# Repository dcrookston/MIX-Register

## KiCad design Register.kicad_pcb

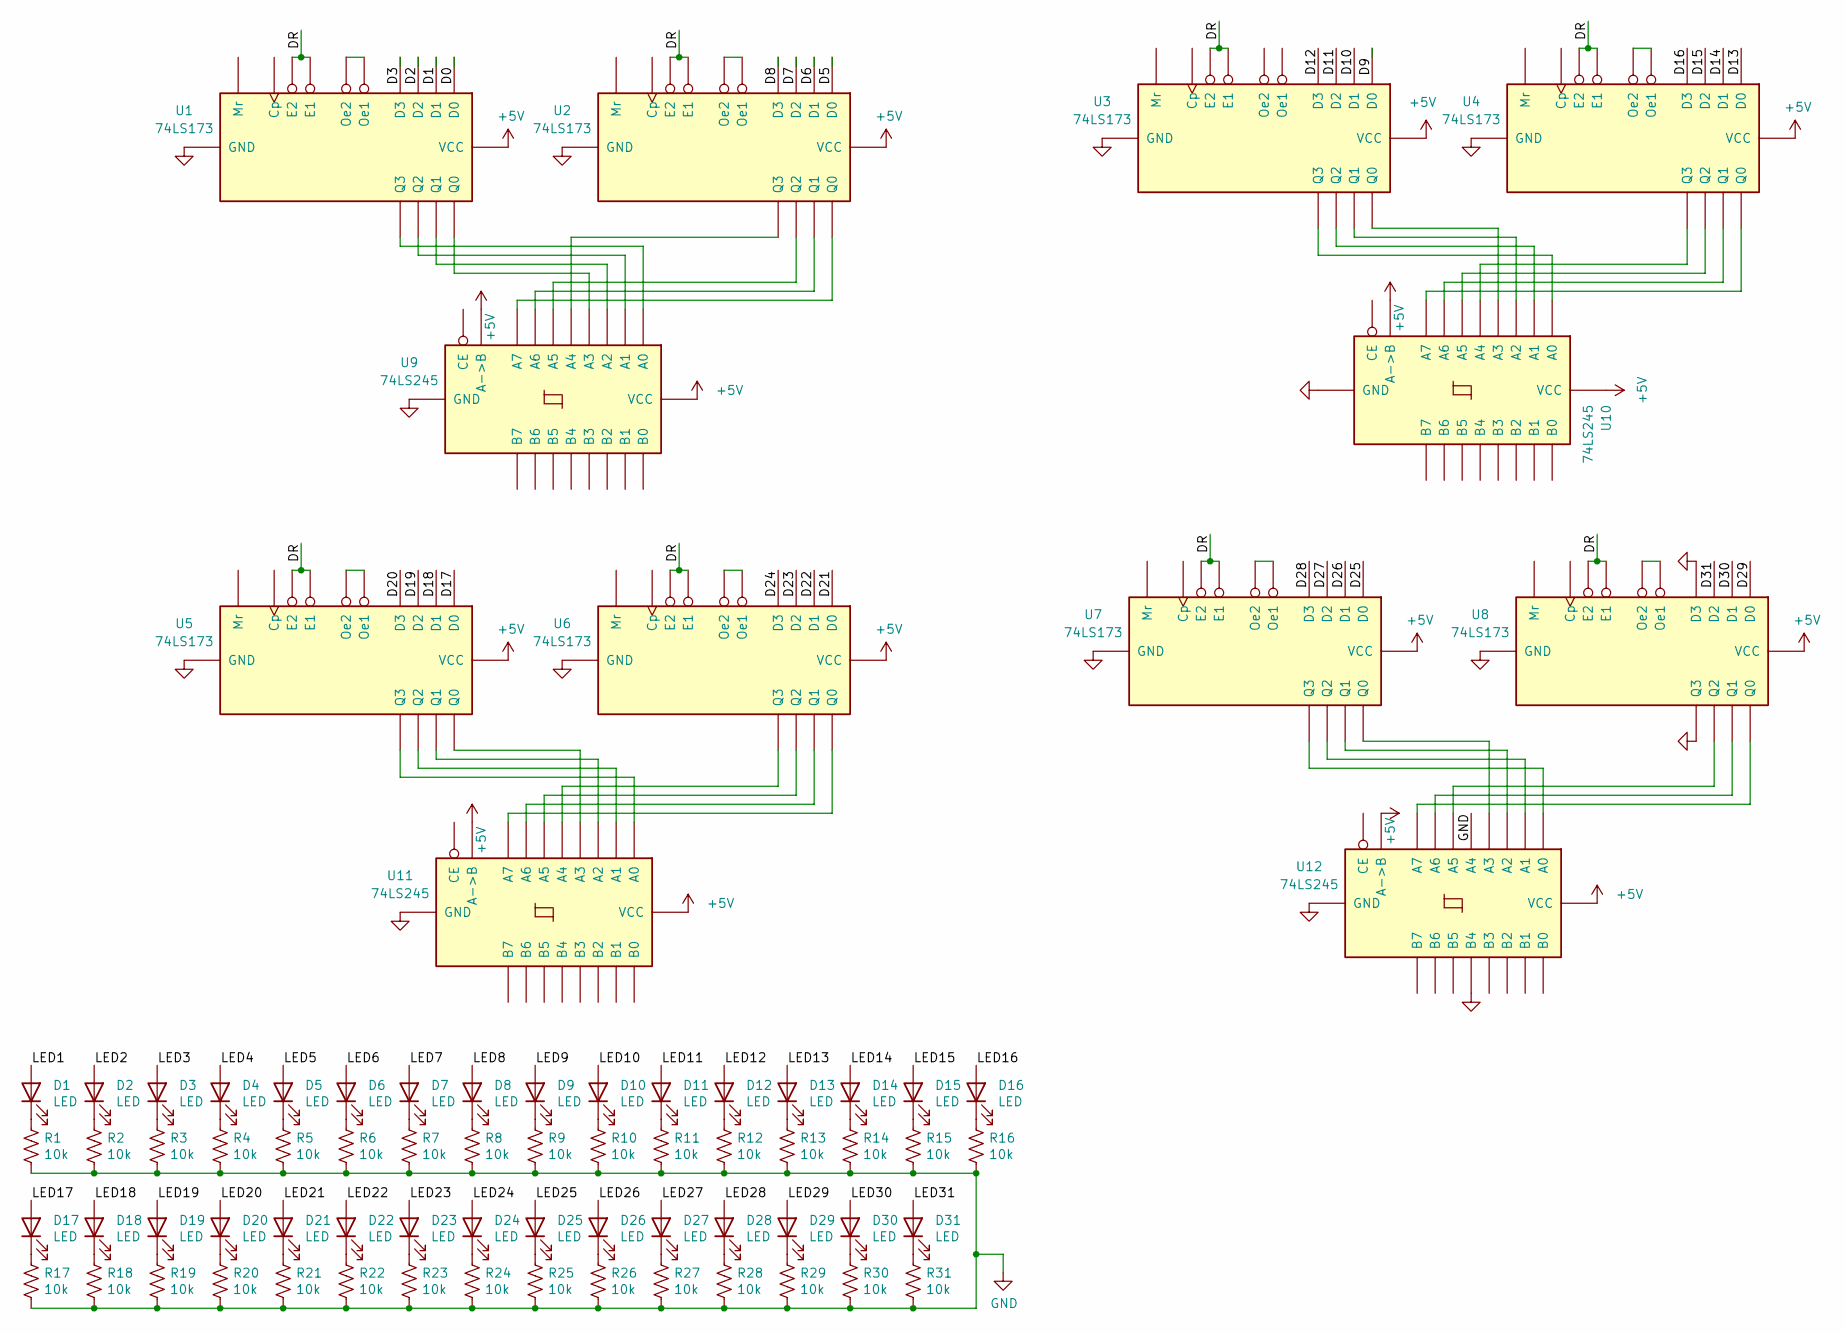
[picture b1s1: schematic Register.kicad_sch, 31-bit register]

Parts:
D1, D2, D3, D4, D5, D6, D7, D8, D9, D10, D11, D12, D13, D14, D15, D16, D17, D18, D19, D20, D21, D22, D23, D24, D25, D26, D27, D28, D29, D30, D31: LED; LED_0402_1005Metric
R1, R2, R3, R4, R5, R6, R7, R8, R9, R10, R11, R12, R13, R14, R15, R16, R17, R18, R19, R20, R21, R22, R23, R24, R25, R26, R27, R28, R29, R30, R31: 10k; R_0402_1005Metric
U1, U2, U3, U4, U5, U6, U7, U8: 74LS173; SOIC-16_3.9x9.9mm_P1.27mm
U9, U10, U11, U12: 74LS245; SOIC-20W_7.5x12.8mm_P1.27mm

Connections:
+5V: U1.16 (VCC), U2.16 (VCC), U3.16 (VCC), U4.16 (VCC), U5.16 (VCC), U6.16 (VCC), U7.16 (VCC), U8.16 (VCC), U9.1 (A->B), U9.20 (VCC), U10.1 (A->B), U10.20 (VCC), U11.1 (A->B), U11.20 (VCC), U12.1 (A->B), U12.20 (VCC)
/D0: U1.14 (D0)
/D1: U1.13 (D1)
/D2: U1.12 (D2)
/D3: U1.11 (D3)
/D5: U2.14 (D0)
/D6: U2.13 (D1)
/D7: U2.12 (D2)
/D8: U2.11 (D3)
/D9: U3.14 (D0)
/D10: U3.13 (D1)
/D11: U3.12 (D2)
/D12: U3.11 (D3)
/D13: U4.14 (D0)
/D14: U4.13 (D1)
/D15: U4.12 (D2)
/D16: U4.11 (D3)
/D17: U5.14 (D0)
/D18: U5.13 (D1)
/D19: U5.12 (D2)
/D20: U5.11 (D3)
/D21: U6.14 (D0)
/D22: U6.13 (D1)
/D23: U6.12 (D2)
/D24: U6.11 (D3)
/D25: U7.14 (D0)
/D26: U7.13 (D1)
/D27: U7.12 (D2)
/D28: U7.11 (D3)
/D29: U8.14 (D0)
/D30: U8.13 (D1)
/D31: U8.12 (D2)
/DR: U1.9 (E1), U1.10 (E2), U2.9 (E1), U2.10 (E2), U3.9 (E1), U3.10 (E2), U4.9 (E1), U4.10 (E2), U5.9 (E1), U5.10 (E2), U6.9 (E1), U6.10 (E2), U7.9 (E1), U7.10 (E2), U8.9 (E1), U8.10 (E2)
/LED1: D1.2 (A)
/LED2: D2.2 (A)
/LED3: D3.2 (A)
/LED4: D4.2 (A)
/LED5: D5.2 (A)
/LED6: D6.2 (A)
/LED7: D7.2 (A)
/LED8: D8.2 (A)
/LED9: D9.2 (A)
/LED10: D10.2 (A)
/LED11: D11.2 (A)
/LED12: D12.2 (A)
/LED13: D13.2 (A)
/LED14: D14.2 (A)
/LED15: D15.2 (A)
/LED16: D16.2 (A)
/LED17: D17.2 (A)
/LED18: D18.2 (A)
/LED19: D19.2 (A)
/LED20: D20.2 (A)
/LED21: D21.2 (A)
/LED22: D22.2 (A)
/LED23: D23.2 (A)
/LED24: D24.2 (A)
/LED25: D25.2 (A)
/LED26: D26.2 (A)
/LED27: D27.2 (A)
/LED28: D28.2 (A)
/LED29: D29.2 (A)
/LED30: D30.2 (A)
/LED31: D31.2 (A)
GND: R1.2, R2.2, R3.2, R4.2, R5.2, R6.2, R7.2, R8.2, R9.2, R10.2, R11.2, R12.2, R13.2, R14.2, R15.2, R16.2, R17.2, R18.2, R19.2, R20.2, R21.2, R22.2, R23.2, R24.2, R25.2, R26.2, R27.2, R28.2, R29.2, R30.2, R31.2, U1.8 (GND), U2.8 (GND), U3.8 (GND), U4.8 (GND), U5.8 (GND), U6.8 (GND), U7.8 (GND), U8.6 (Q3), U8.8 (GND), U8.11 (D3), U9.10 (GND), U10.10 (GND), U11.10 (GND), U12.6 (A4), U12.10 (GND), U12.14 (B4)
unnamed: D1.1 (K), R1.1
unnamed: D2.1 (K), R2.1
unnamed: D3.1 (K), R3.1
unnamed: D4.1 (K), R4.1
unnamed: D5.1 (K), R5.1
unnamed: D6.1 (K), R6.1
unnamed: D7.1 (K), R7.1
unnamed: D8.1 (K), R8.1
unnamed: D9.1 (K), R9.1
unnamed: D10.1 (K), R10.1
unnamed: D11.1 (K), R11.1
unnamed: D12.1 (K), R12.1
unnamed: D13.1 (K), R13.1
unnamed: D14.1 (K), R14.1
unnamed: D15.1 (K), R15.1
unnamed: D16.1 (K), R16.1
unnamed: D17.1 (K), R17.1
unnamed: D18.1 (K), R18.1
unnamed: D19.1 (K), R19.1
unnamed: D20.1 (K), R20.1
unnamed: D21.1 (K), R21.1
unnamed: D22.1 (K), R22.1
unnamed: D23.1 (K), R23.1
unnamed: D24.1 (K), R24.1
unnamed: D25.1 (K), R25.1
unnamed: D26.1 (K), R26.1
unnamed: D27.1 (K), R27.1
unnamed: D28.1 (K), R28.1
unnamed: D29.1 (K), R29.1
unnamed: D30.1 (K), R30.1
unnamed: D31.1 (K), R31.1
unnamed: U1.1 (Oe1), U1.2 (Oe2)
unnamed: U1.3 (Q0), U9.5 (A3)
unnamed: U1.4 (Q1), U9.4 (A2)
unnamed: U1.5 (Q2), U9.3 (A1)
unnamed: U1.6 (Q3), U9.2 (A0)
unnamed: U2.1 (Oe1), U2.2 (Oe2)
unnamed: U2.3 (Q0), U9.9 (A7)
unnamed: U2.4 (Q1), U9.8 (A6)
unnamed: U2.5 (Q2), U9.7 (A5)
unnamed: U2.6 (Q3), U9.6 (A4)
unnamed: U4.1 (Oe1), U4.2 (Oe2)
unnamed: U5.1 (Oe1), U5.2 (Oe2)
unnamed: U6.1 (Oe1), U6.2 (Oe2)
unnamed: U7.1 (Oe1), U7.2 (Oe2)
unnamed: U8.1 (Oe1), U8.2 (Oe2)
unnamed: U3.6 (Q3), U10.2 (A0)
unnamed: U3.5 (Q2), U10.3 (A1)
unnamed: U3.4 (Q1), U10.4 (A2)
unnamed: U3.3 (Q0), U10.5 (A3)
unnamed: U4.6 (Q3), U10.6 (A4)
unnamed: U4.5 (Q2), U10.7 (A5)
unnamed: U4.4 (Q1), U10.8 (A6)
unnamed: U4.3 (Q0), U10.9 (A7)
unnamed: U5.6 (Q3), U11.2 (A0)
unnamed: U5.5 (Q2), U11.3 (A1)
unnamed: U5.4 (Q1), U11.4 (A2)
unnamed: U5.3 (Q0), U11.5 (A3)
unnamed: U6.6 (Q3), U11.6 (A4)
unnamed: U6.5 (Q2), U11.7 (A5)
unnamed: U6.4 (Q1), U11.8 (A6)
unnamed: U6.3 (Q0), U11.9 (A7)
unnamed: U7.6 (Q3), U12.2 (A0)
unnamed: U7.5 (Q2), U12.3 (A1)
unnamed: U7.4 (Q1), U12.4 (A2)
unnamed: U7.3 (Q0), U12.5 (A3)
unnamed: U8.5 (Q2), U12.7 (A5)
unnamed: U8.4 (Q1), U12.8 (A6)
unnamed: U8.3 (Q0), U12.9 (A7)

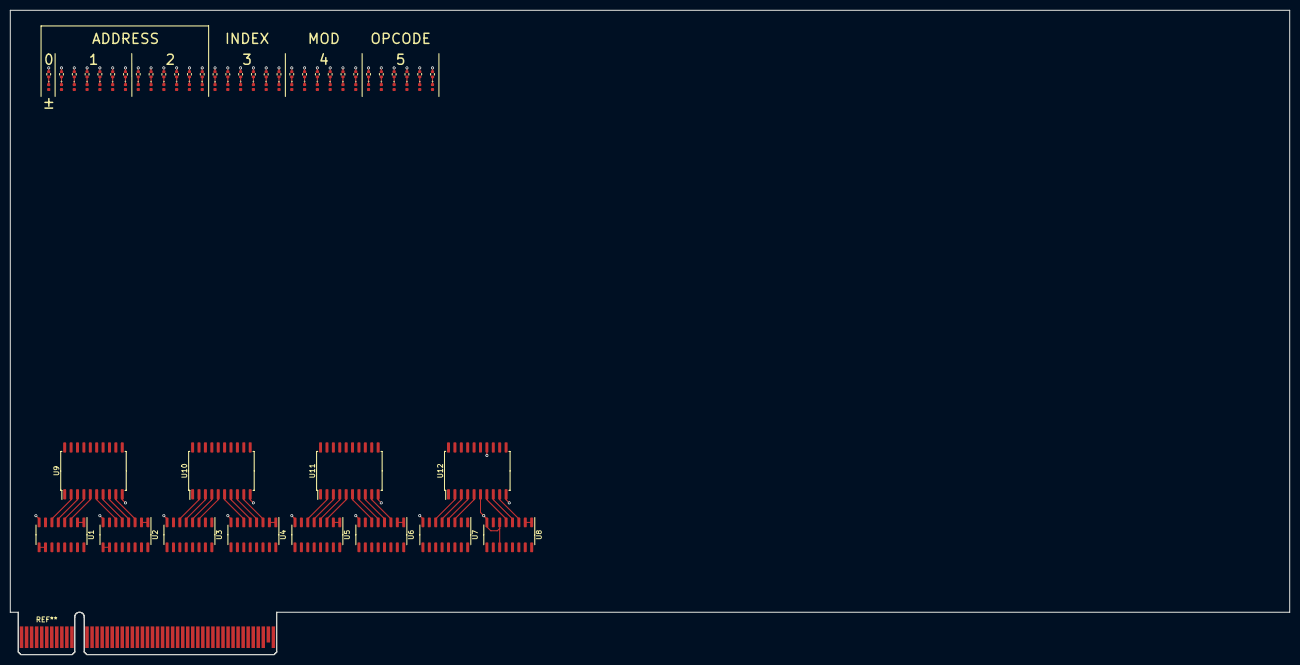
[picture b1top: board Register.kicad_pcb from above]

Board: 2 copper layers, 254.0 x 127.9 mm, 74 parts (0 on the bottom side), 72 nets.

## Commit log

2023-07-07 initial check-in
    Initial check-in of an early version
2023-07-07 Connect and organize Q lines
2023-07-07 update gitignore
2023-07-07 Added footprints
    Added footprints for 74LS245s (SOIC 20, 12.8x7.5mm, 1.27mm pitch)
2023-08-01 Fixed wiring issues
    The registers weren't connected to the bus xcvr correctly, so I rewired the connections between them. The new connections allow for a much better physical layout.
2023-08-01 Update PCB
    Updated PCB with recent rewiring changes
2023-08-02 Rearranged registers and xcvrs
    Moved registers and bus transceivers into position relative to one another.
    Also moved LED grounding vias off of solder pads.
